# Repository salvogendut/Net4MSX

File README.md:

# Net4MSX

An MSX cartridge project providing Ethernet through a **W5100S module** and a
**TCP/IP UNAPI** driver. A Raspberry Pi Pico is an optional candidate for bus
interfacing or supporting firmware; it is not yet a required component.

The project is at the architecture stage, with design requirements, an editable
KiCad concept and a 3D placement mockup. Firmware and a routed, qualified PCB
remain to be developed.

## Starting design

- Compare Net4CPC-style direct parallel access with a Pico command coprocessor,
  informed by ESP8266-UNAPI-Firmware's small Z80 front end.
- Expose TCP/IP UNAPI 1.1 to MSX applications, using the W5100S socket engine.
- Use MSXDiagCartridge as the connector, ROM and mechanical reference.
- Use Net4CPC's generic SPI/parallel module footprint as requested for the user's
  W5100S module. Confirm its physical pinout before completing the circuit.

## Documentation

- [Architecture and decisions](docs/ARCHITECTURE.md)
- [Hardware requirements and cartridge pinout](docs/HARDWARE.md)
- [W5100S vendor documentation and integration requirements](docs/W5100S.md)
- [UNAPI implementation scope](docs/UNAPI.md)
- [Development roadmap and acceptance criteria](docs/ROADMAP.md)
- [Reference repositories and provenance](docs/REFERENCES.md)
- [ESP8266 firmware reassessment](docs/ESP8266-REASSESSMENT.md)
- [Pinned Z80 driver and ioLibrary review](docs/SOFTWARE-REVIEW.md)
- [MSX–Pico mailbox protocol proposal](docs/MAILBOX-PROTOCOL.md)
- [Executable mailbox model and conformance tests](docs/MAILBOX-MODEL.md)
- [Pico and direct-parallel resource budgets](docs/RESOURCE-BUDGET.md)
- [KiCad concept and 3D mockup](hardware/README.md)

The mailbox now has a host-side Python model and fake-backend conformance tests:

```sh
python3 -m unittest discover -s tests -v
```

The next software step is a reproducible minimal Z80/Pico build with measured
ROM/RAM use. Module selection, MSX register mapping and reliable bus/register
access on a physical prototype remain hardware gates. No assembler or firmware
SDK has been selected yet; the resource budgets are design allocations, not
measured firmware sizes. The model uses Python 3.10+ and the standard library.

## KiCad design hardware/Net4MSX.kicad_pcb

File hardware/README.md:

# Net4MSX KiCad concept A0

Open [Net4MSX.kicad_pro](Net4MSX.kicad_pro) with KiCad 6 or later.

- [Schematic](Net4MSX.kicad_sch): self-contained connector/module symbols and
  proposed Pico-to-W5100S SPI connections.
- [PCB](Net4MSX.kicad_pcb): editable placement, 50-contact edge, module/Pico
  footprints, board outline and reserved bus/ROM/power areas.
- [3D mockup](renders/Net4MSX-concept-3d.png) and
  [top view](renders/Net4MSX-concept-top.png).
- [Blender scene](Net4MSX-concept.blend): editable geometric rendering.
- [Pin map](pin-map.csv): schematic/PCB mapping for review.
- [Footprint library](Net4MSX.pretty), [symbol library](Net4MSX.kicad_sym)
  and simple [3D models](models).

## What this design establishes

The module footprint is adapted from Net4CPC's generic W5100S SPI/parallel
module, as requested by the user. It has two rows of 16 pad positions, 2.54 mm
pitch and 25.4 mm row spacing. The source's eight unassigned pad positions
(13–20) are preserved as unconnected pads; their physical purpose must be checked
on the actual module. They are not treated as additional W5100S signals.

The concept illustrates the Pico command-coprocessor alternative described in
[Architecture](../docs/ARCHITECTURE.md). This is not a final selection against
direct parallel access. Proposed SPI wiring is:

| Pico GPIO (physical pin) | Net4CPC module pad | Signal |
| --- | --- | --- |
| GP16 (21) | 32 | MISO |
| GP17 (22) | 29 | /CS |
| GP18 (24) | 30 | SCLK |
| GP19 (25) | 31 | MOSI |
| GP20 (26) | 12 | /RESET |
| GP21 (27) | 11 | /INT |

Module MODE (28) is assigned ground for SPI. /RD and /WR (1, 2) are assigned
the module's 3.3 V rail. Parallel data pads have separate unused nets. Module
and Pico 3.3 V rails are separate; their regulator outputs are not tied together.
Pico signal numbering follows the
[official Pico pinout](https://datasheets.raspberrypi.com/pico/Pico-R3-A4-Pinout.pdf).

The [W5100S integration notes](../docs/W5100S.md) record the vendor baseline,
mode-strap review and SPI read erratum. These requirements still need validation
on the user's module; the concept wiring and footprint are provisional.

The carrier envelope is a **proposed 80 × 90 mm**, 1.6 mm board with a
65.44 mm contact tongue. It is not a measured replacement for the diagnostic
cartridge shell. The 25-per-side contact pitch and approximate contact geometry
were checked against the diagnostic cartridge Gerbers. Board outline, insertion
depth, edge numbering/orientation and shell fit still need physical verification.
Component-side copper is F.Cu; looking at that side with the tongue down, the
even contacts run 50 to 2 from left to right. Back-side odd contacts share those
physical positions, 49 to 1 in the same top-view coordinates.

## Completion boundary

This is an **unrouted interface and placement concept, not a manufacturing
release**. The schematic intentionally leaves `5V_SLOT`, `MOD_5V_INPUT` and
`PICO_VSYS` separate. It does not yet implement supply protection, power
sequencing, USB backfeed prevention, pull-ups, boot-safe output enables, MSX
level translation, bus decoding, mailbox/FIFO, ROM or workspace circuitry.
Reserved areas on the PCB are planning annotations, not populated circuits.

The schematic uses passive interface symbols to describe pin mapping; an ERC
pass would not establish electrical correctness. No full ERC/DRC acceptance or
hardware test is claimed. There are no copper tracks or manufacturing Gerbers.

The 3D scene is generated from the PCB placement export, with simplified module,
RJ45, Pico and socket shapes. Small module components are illustrative. It is a
placement mockup, not a vendor-accurate mechanical model; connector height and
module clearances need measurement. KiCad also has local VRML placeholder models
for U1/U2 so its built-in 3D viewer can display the concept.

## Regeneration

Validation performed: KiCad 6 schematic opening, PCB/footprint reload, 122-pad
schematic/PCB/CSV agreement, distinct pad positions and expected header extents,
placement agreement with the render input, and visual inspection of both renders.

The checked-in CAD files open without the reference checkout. Regeneration uses
Python 3 with KiCad 6's `pcbnew` module and Blender 3.4:

```sh
python3 tools/generate_hardware.py --net4cpc /path/to/Net4CPC
blender -b --python tools/render_board.py
python3 tools/check_hardware.py
```

Run from the repository root. The generator overwrites the generated CAD files;
preserve any manual changes before running it. `placement.json` is produced from
the KiCad board and consumed by Blender, keeping footprint locations aligned.
See [NOTICE](NOTICE.md) for provenance and retained licenses.

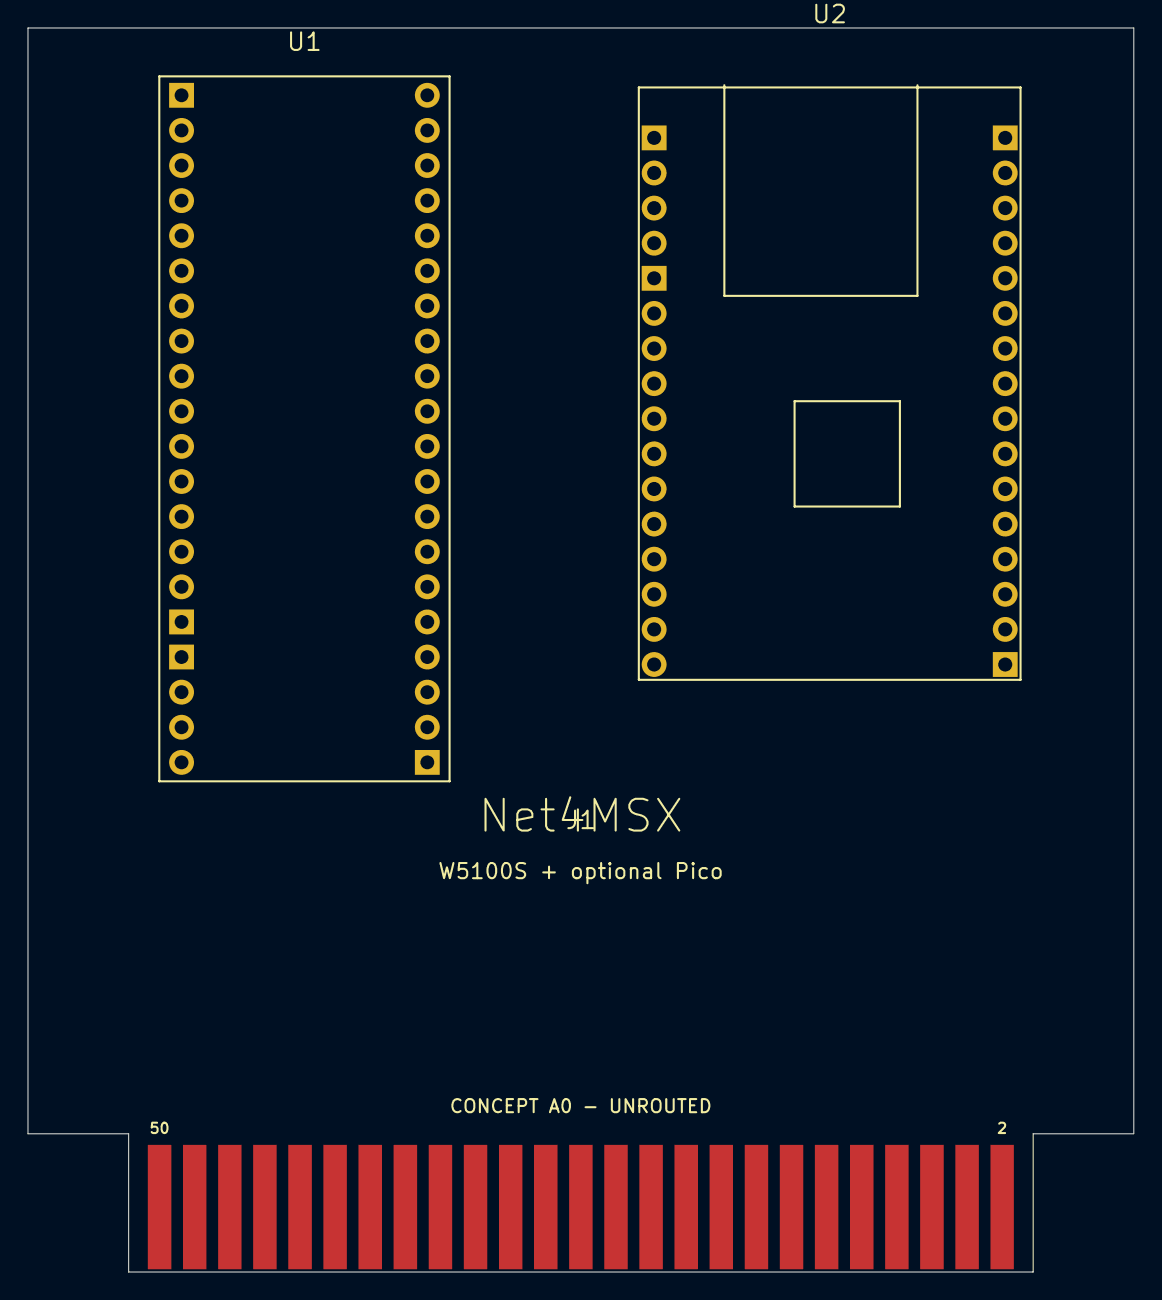
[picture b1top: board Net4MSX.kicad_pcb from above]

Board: 2 copper layers, 80.0 x 90.0 mm, 3 parts (0 on the bottom side), 10 nets, no tracks yet.

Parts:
J1: MSX cartridge edge - orientation review required; MSX_Edge_50_Concept
U1: Raspberry Pi Pico - optional coprocessor; Pico_ThroughHole_Concept
U2: W5100S SPI/parallel module - Net4CPC; W5100S_Net4CPC

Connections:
5V_SLOT: J1.45, J1.47
GND: J1.41, J1.43, U1.3, U1.8, U1.13, U1.18, U1.23, U1.28, U1.33, U1.38, U2.25, U2.26, U2.27, U2.28
MOD_3V3: U2.1, U2.2, U2.23, U2.24
MOD_5V_INPUT: U2.21, U2.22
SPI_MISO: U1.21, U2.32
SPI_MOSI: U1.25, U2.31
SPI_SCK: U1.24, U2.30
SPI_nCS: U1.22, U2.29
WIZ_nINT: U1.27, U2.11
WIZ_nRESET: U1.26, U2.12
